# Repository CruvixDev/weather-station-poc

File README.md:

# Weather station POC (Proof Of Concept)

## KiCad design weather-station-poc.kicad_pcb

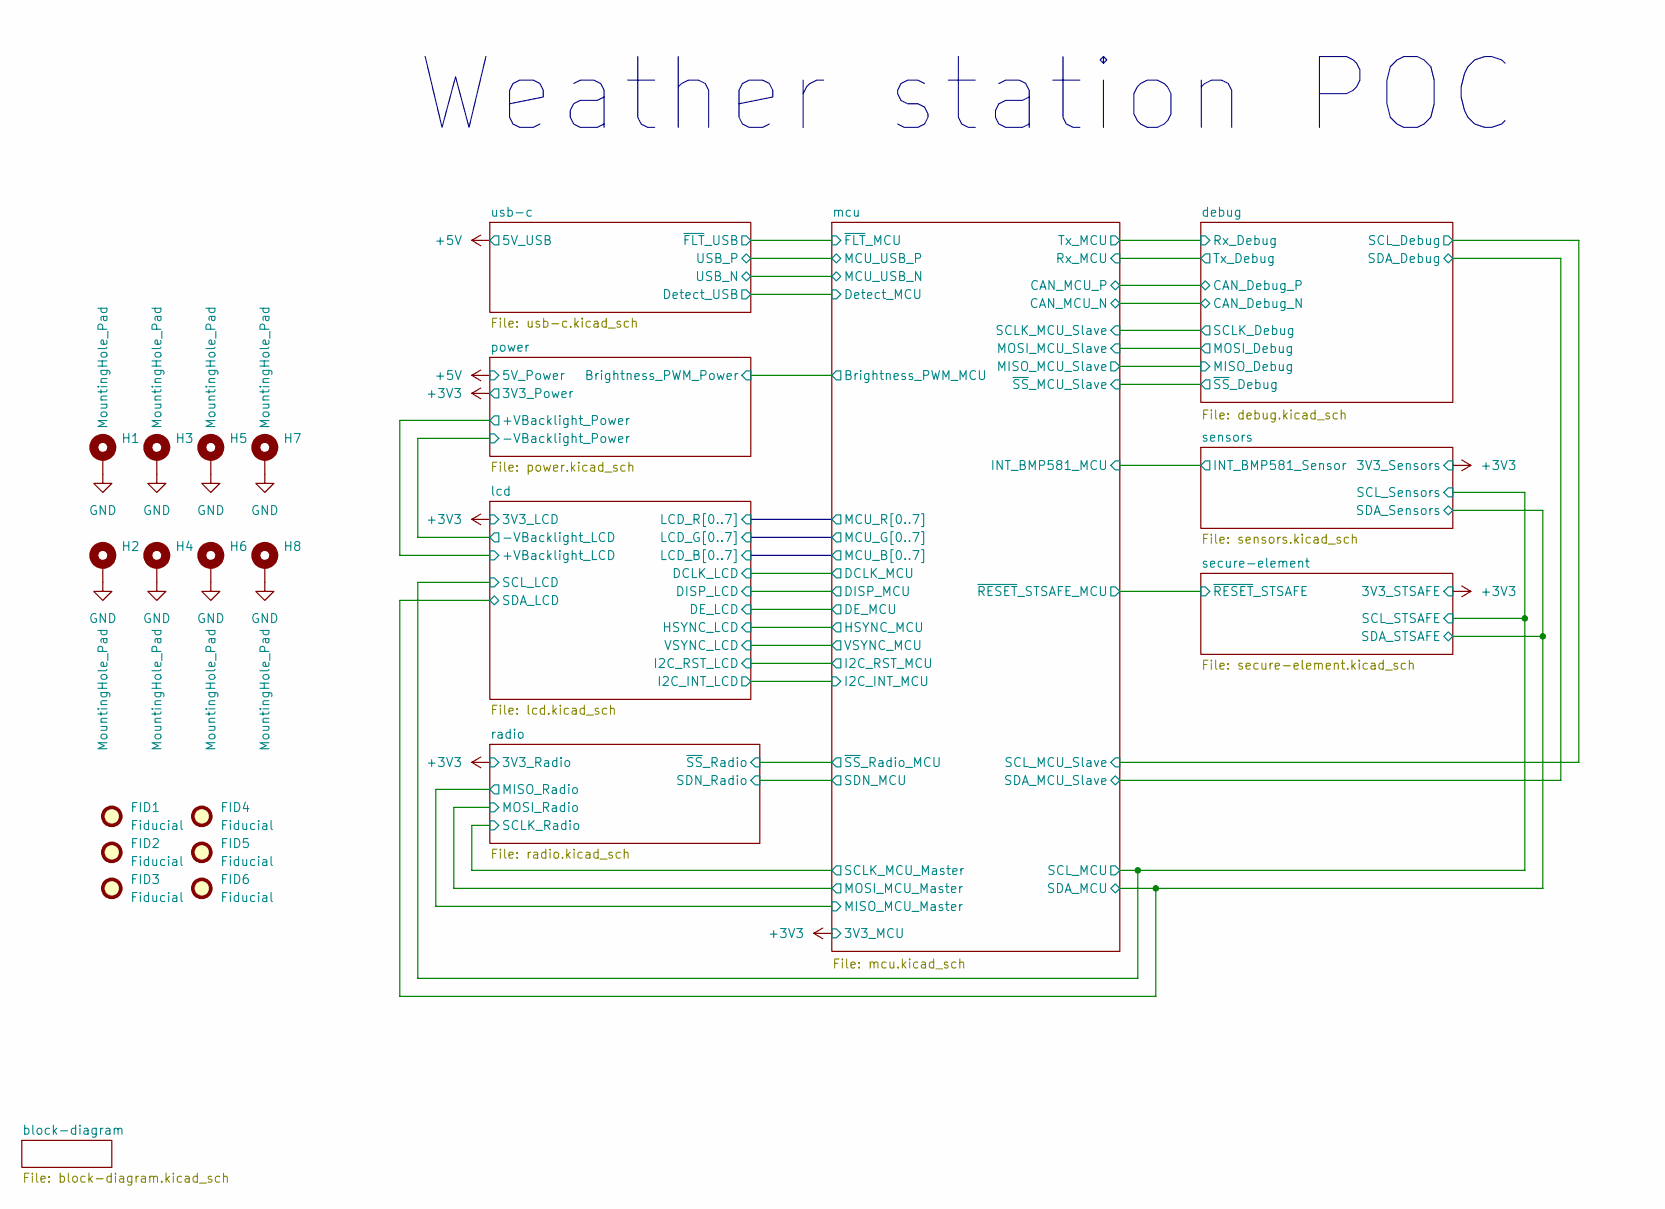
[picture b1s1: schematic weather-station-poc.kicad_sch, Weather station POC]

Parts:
FID1, FID2, FID3, FID4, FID5, FID6: Fiducial; Fiducial_1mm_Mask2mm; Manufacturer_Part_Number N/A
H1, H2, H3, H4, H5, H6, H7, H8: MountingHole_Pad; MountingHole_3.5mm_Pad_Via; Manufacturer_Part_Number N/A

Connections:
GND: H1.1 (1_1), H2.1 (1_1), H3.1 (1_1), H4.1 (1_1), H5.1 (1_1), H6.1 (1_1), H7.1 (1_1), H8.1 (1_1); also elsewhere on the board

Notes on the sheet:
Weather station POC

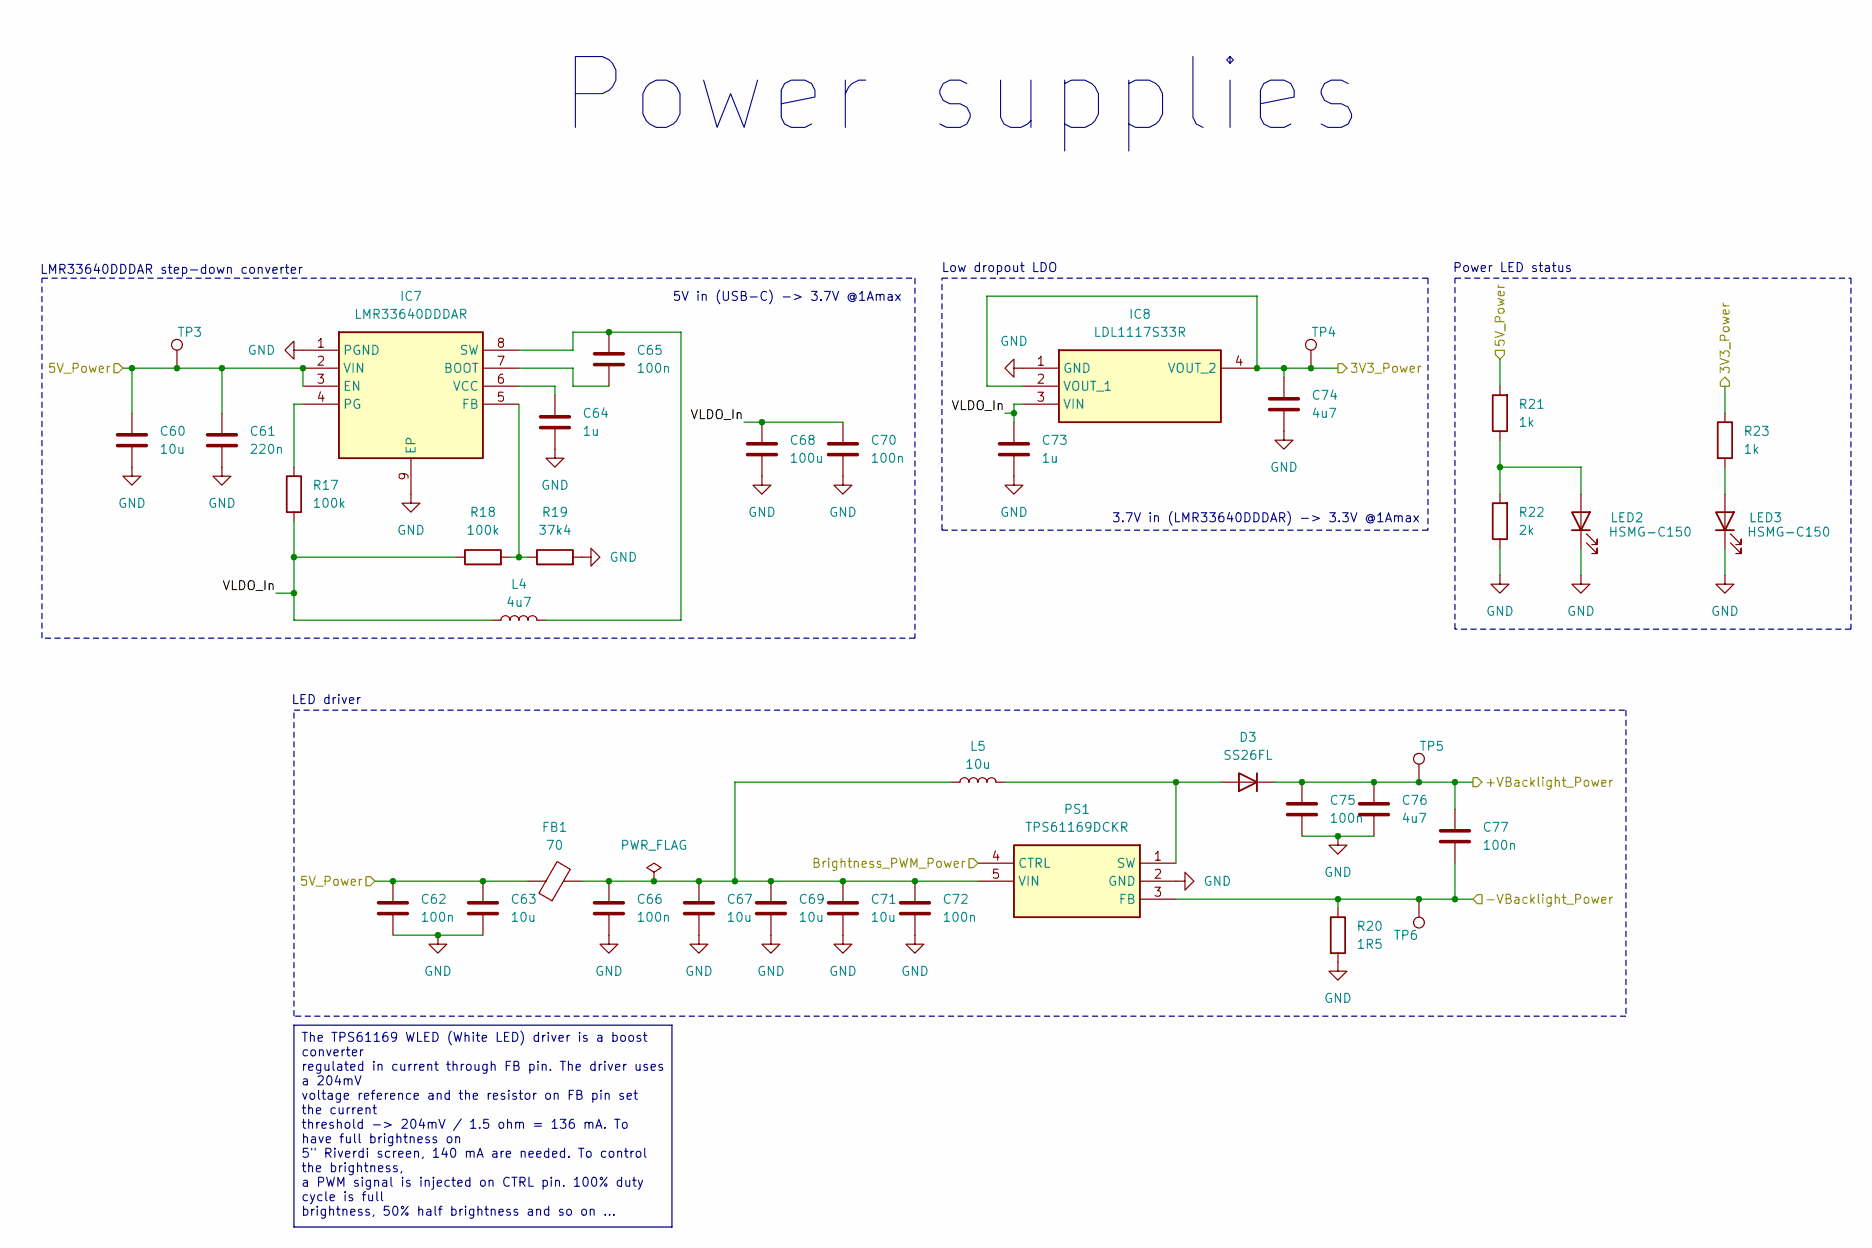
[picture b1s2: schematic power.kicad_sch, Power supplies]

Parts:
C60: 10u; C_0805_2012Metric_Pad1.18x1.45mm_HandSolder; Manufacturer_Part_Number C0805C106K8PACTU
C61: 220n; C_0402_1005Metric_Pad0.74x0.62mm_HandSolder; Manufacturer_Part_Number GRM155R61A224KE19D
C62, C66, C72, C75, C77: 100n; C_0603_1608Metric_Pad1.08x0.95mm_HandSolder; Manufacturer_Part_Number 885012206020
C63, C67, C69, C71: 10u; C_0603_1608Metric_Pad1.08x0.95mm_HandSolder; Manufacturer_Part_Number GRM188Z71A106KA73D
C64: 1u; C_0603_1608Metric_Pad1.08x0.95mm_HandSolder; Manufacturer_Part_Number GRM188R60J105KA01D
C65: 100n; C_0402_1005Metric_Pad0.74x0.62mm_HandSolder; Manufacturer_Part_Number GRM155R71A104KA01D
C68: 100u; C_1210_3225Metric_Pad1.33x2.70mm_HandSolder; Manufacturer_Part_Number GRM32EC80J107ME20L
C70: 100n; C_0603_1608Metric_Pad1.08x0.95mm_HandSolder; Manufacturer_Part_Number CGA3E2X7R1H104K080AA
C73: 1u; C_0603_1608Metric_Pad1.08x0.95mm_HandSolder; Manufacturer_Part_Number 885012206026
C74, C76: 4u7; C_0603_1608Metric_Pad1.08x0.95mm_HandSolder; Manufacturer_Part_Number GRM188Z71A475KE15J
D3: SS26FL; SODFL3617X108N; Mouser Part Number 512-SS26FL
FB1: 70; L_0603_1608Metric_Pad1.05x0.95mm_HandSolder; Part number BLM18SG700TN1D
IC7: LMR33640DDDAR; SOIC127P600X170-9N; Mouser Part Number 595-LMR33640DDDAR
IC8: LDL1117S33R; SOT230P700X180-4N; Mouser Part Number 511-LDL1117S33R
L4: 4u7; EXL1V06064R7R; Manufacturer_Part_Number EXL1V0606-4R7-R
L5: 10u; INDPM4040X180N; Manufacturer_Part_Number 74404042100
LED2, LED3: HSMG-C150; LEDC3216X120N; Mouser Part Number 630-HSMG-C150
PS1: TPS61169DCKR; SOT65P210X110-5N; Mouser Part Number 595-TPS61169DCKR
R17: 100k; R_0603_1608Metric_Pad0.98x0.95mm_HandSolder; Manufacturer_Part_Number CRCW0603100KFKEA
R18: 100k; R_0402_1005Metric_Pad0.72x0.64mm_HandSolder; Manufacturer_Part_Number CRCW0402100KFKED
R19: 37k4; R_0402_1005Metric_Pad0.72x0.64mm_HandSolder; Manufacturer_Part_Number CRCW040237K4FKED
R20: 1R5; R_0603_1608Metric_Pad0.98x0.95mm_HandSolder; Manufacturer_Part_Number ERJ-H3QD1R50V
R21, R23: 1k; R_0603_1608Metric_Pad0.98x0.95mm_HandSolder; Manufacturer_Part_Number 560112116014
R22: 2k; R_0603_1608Metric_Pad0.98x0.95mm_HandSolder; Manufacturer_Part_Number 560112116058
TP3, TP4, TP5, TP6: TestPoint; 5015; Manufacturer_Part_Number N/A

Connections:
+3V3: C74.1, IC8.2 (VOUT_1), IC8.4 (VOUT_2), R23.1, TP4.1 (1_1); also elsewhere on the board
+5V: C60.1, C61.1, C62.1, C63.1, FB1.1, IC7.2 (VIN), IC7.3 (EN), R21.2, TP3.1 (1_1); also elsewhere on the board
/lcd/+VBacklight_LCD: C75.1, C76.1, C77.1, D3.1 (K), TP5.1 (1_1); also elsewhere on the board
/lcd/-VBacklight_LCD: C77.2, PS1.3 (FB), R20.1, TP6.1 (1_1); also elsewhere on the board
/mcu/Brightness_PWM_MCU: PS1.4 (CTRL); also elsewhere on the board
/power/VLDO_In: C68.1, C70.1, C73.1, IC8.3 (VIN), L4.1, R17.2, R18.1
GND: C60.2, C61.2, C62.2, C63.2, C64.2, C66.2, C67.2, C68.2, C69.2, C70.2, C71.2, C72.2, C73.2, C74.2, C75.2, C76.2, IC7.1 (PGND), IC7.9 (EP), IC8.1 (GND), LED2.1 (K), LED3.1 (K), PS1.2 (GND), R19.2, R20.2, R22.1; also elsewhere on the board
unnamed: D3.2 (A), L5.2, PS1.1 (SW)
unnamed: C65.2, IC7.7 (BOOT)
unnamed: IC7.5 (FB), R18.2, R19.1
unnamed: IC7.4 (PG), R17.1
unnamed: C65.1, IC7.8 (SW), L4.2
unnamed: C64.1, IC7.6 (VCC)
unnamed: LED2.2 (A), R21.1, R22.2
unnamed: LED3.2 (A), R23.2
unnamed: C66.1, C67.1, C69.1, C71.1, C72.1, FB1.2, L5.1, PS1.5 (VIN)

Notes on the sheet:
Power supplies
3.7V in (LMR33640DDDAR) -> 3.3V @1Amax
LED driver
Low dropout LDO
LMR33640DDDAR step-down converter
5V in (USB-C) -> 3.7V @1Amax
Power LED status
The TPS61169 WLED (White LED) driver is a boost converter regulated in current through FB pin. The driver uses a 204mV voltage reference and the resistor on FB pin set the current threshold -> 204mV / 1.5 ohm = 136 mA. To have full brightness on 5" Riverdi screen, 140 mA are needed. To control the 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

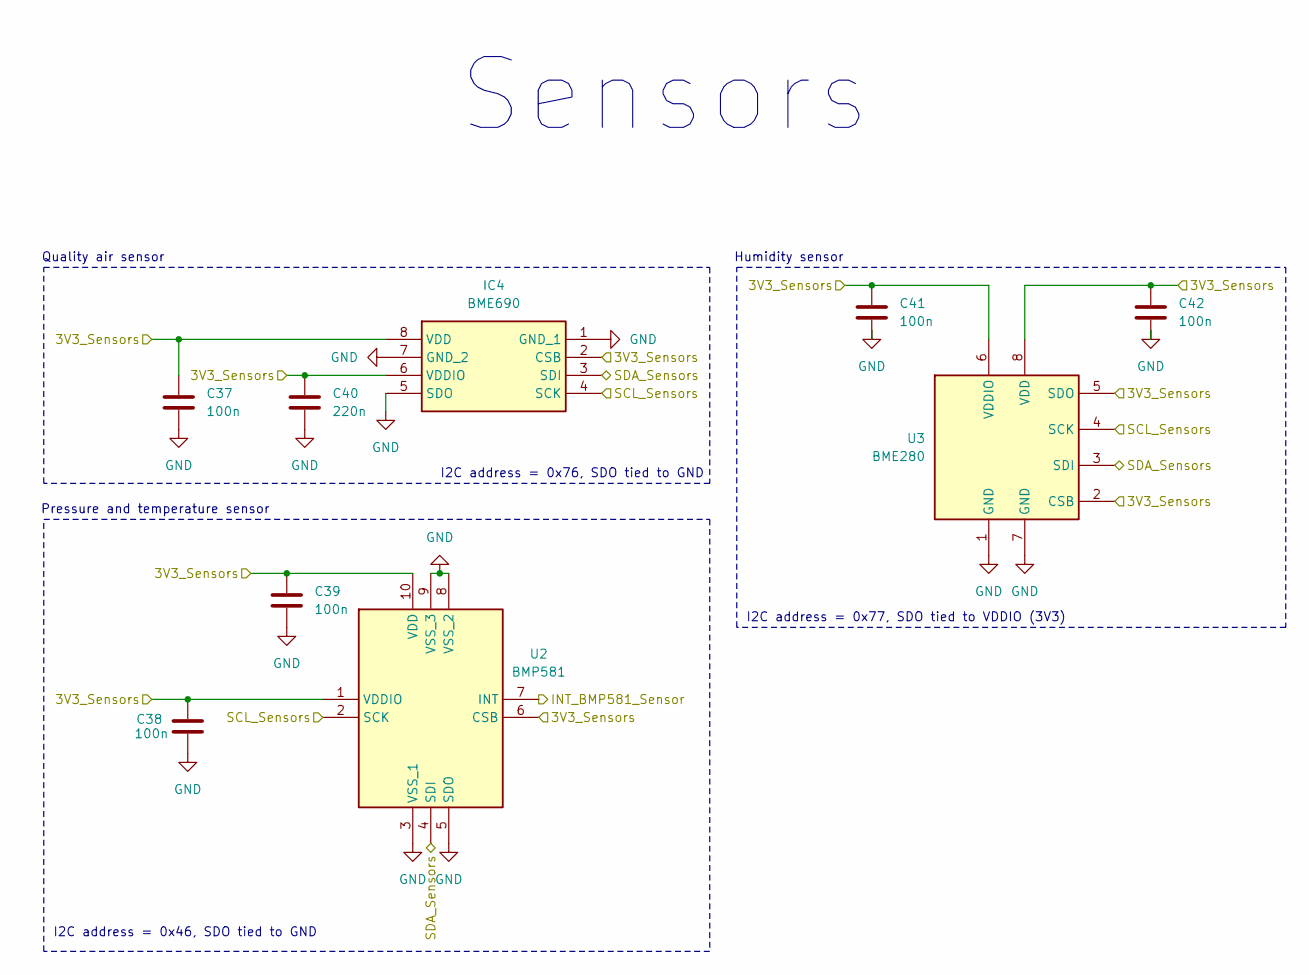
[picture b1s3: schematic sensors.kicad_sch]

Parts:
C37, C38, C39, C41, C42: 100n; C_0603_1608Metric_Pad1.08x0.95mm_HandSolder; Manufacturer_Part_Number 885012206020
C40: 220n; C_0603_1608Metric_Pad1.08x0.95mm_HandSolder; Manufacturer_Part_Number 885012206022
IC4: BME690; Mouser Part Number 262-BME690
U2: BMP581; Mouser Part Number 262-BMP581
U3: BME280; Bosch_LGA-8_2.5x2.5mm_P0.65mm_ClockwisePinNumbering; Manufacturer_Part_Number BME280

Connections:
+3V3: C37.1, C38.1, C39.1, C40.1, C41.1, C42.1, IC4.2 (CSB), IC4.6 (VDDIO), IC4.8 (VDD), U2.1 (VDDIO), U2.6 (CSB), U2.10 (VDD), U3.2 (CSB), U3.5 (SDO), U3.6 (VDDIO), U3.8 (VDD); also elsewhere on the board
/lcd/SCL_LCD: IC4.4 (SCK), U2.2 (SCK), U3.4 (SCK); also elsewhere on the board
/lcd/SDA_LCD: IC4.3 (SDI), U2.4 (SDI), U3.3 (SDI); also elsewhere on the board
/mcu/INT_BMP581_MCU: U2.7 (INT); also elsewhere on the board
GND: C37.2, C38.2, C39.2, C40.2, C41.2, C42.2, IC4.1 (GND_1), IC4.5 (SDO), IC4.7 (GND_2), U2.3 (VSS_1), U2.5 (SDO), U2.8 (VSS_2), U2.9 (VSS_3), U3.1 (GND), U3.7 (GND); also elsewhere on the board

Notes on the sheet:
I2C address = 0x77, SDO tied to VDDIO (3V3)
Humidity sensor
Pressure and temperature sensor
I2C address = 0x46, SDO tied to GND
Sensors
Quality air sensor
I2C address = 0x76, SDO tied to GND

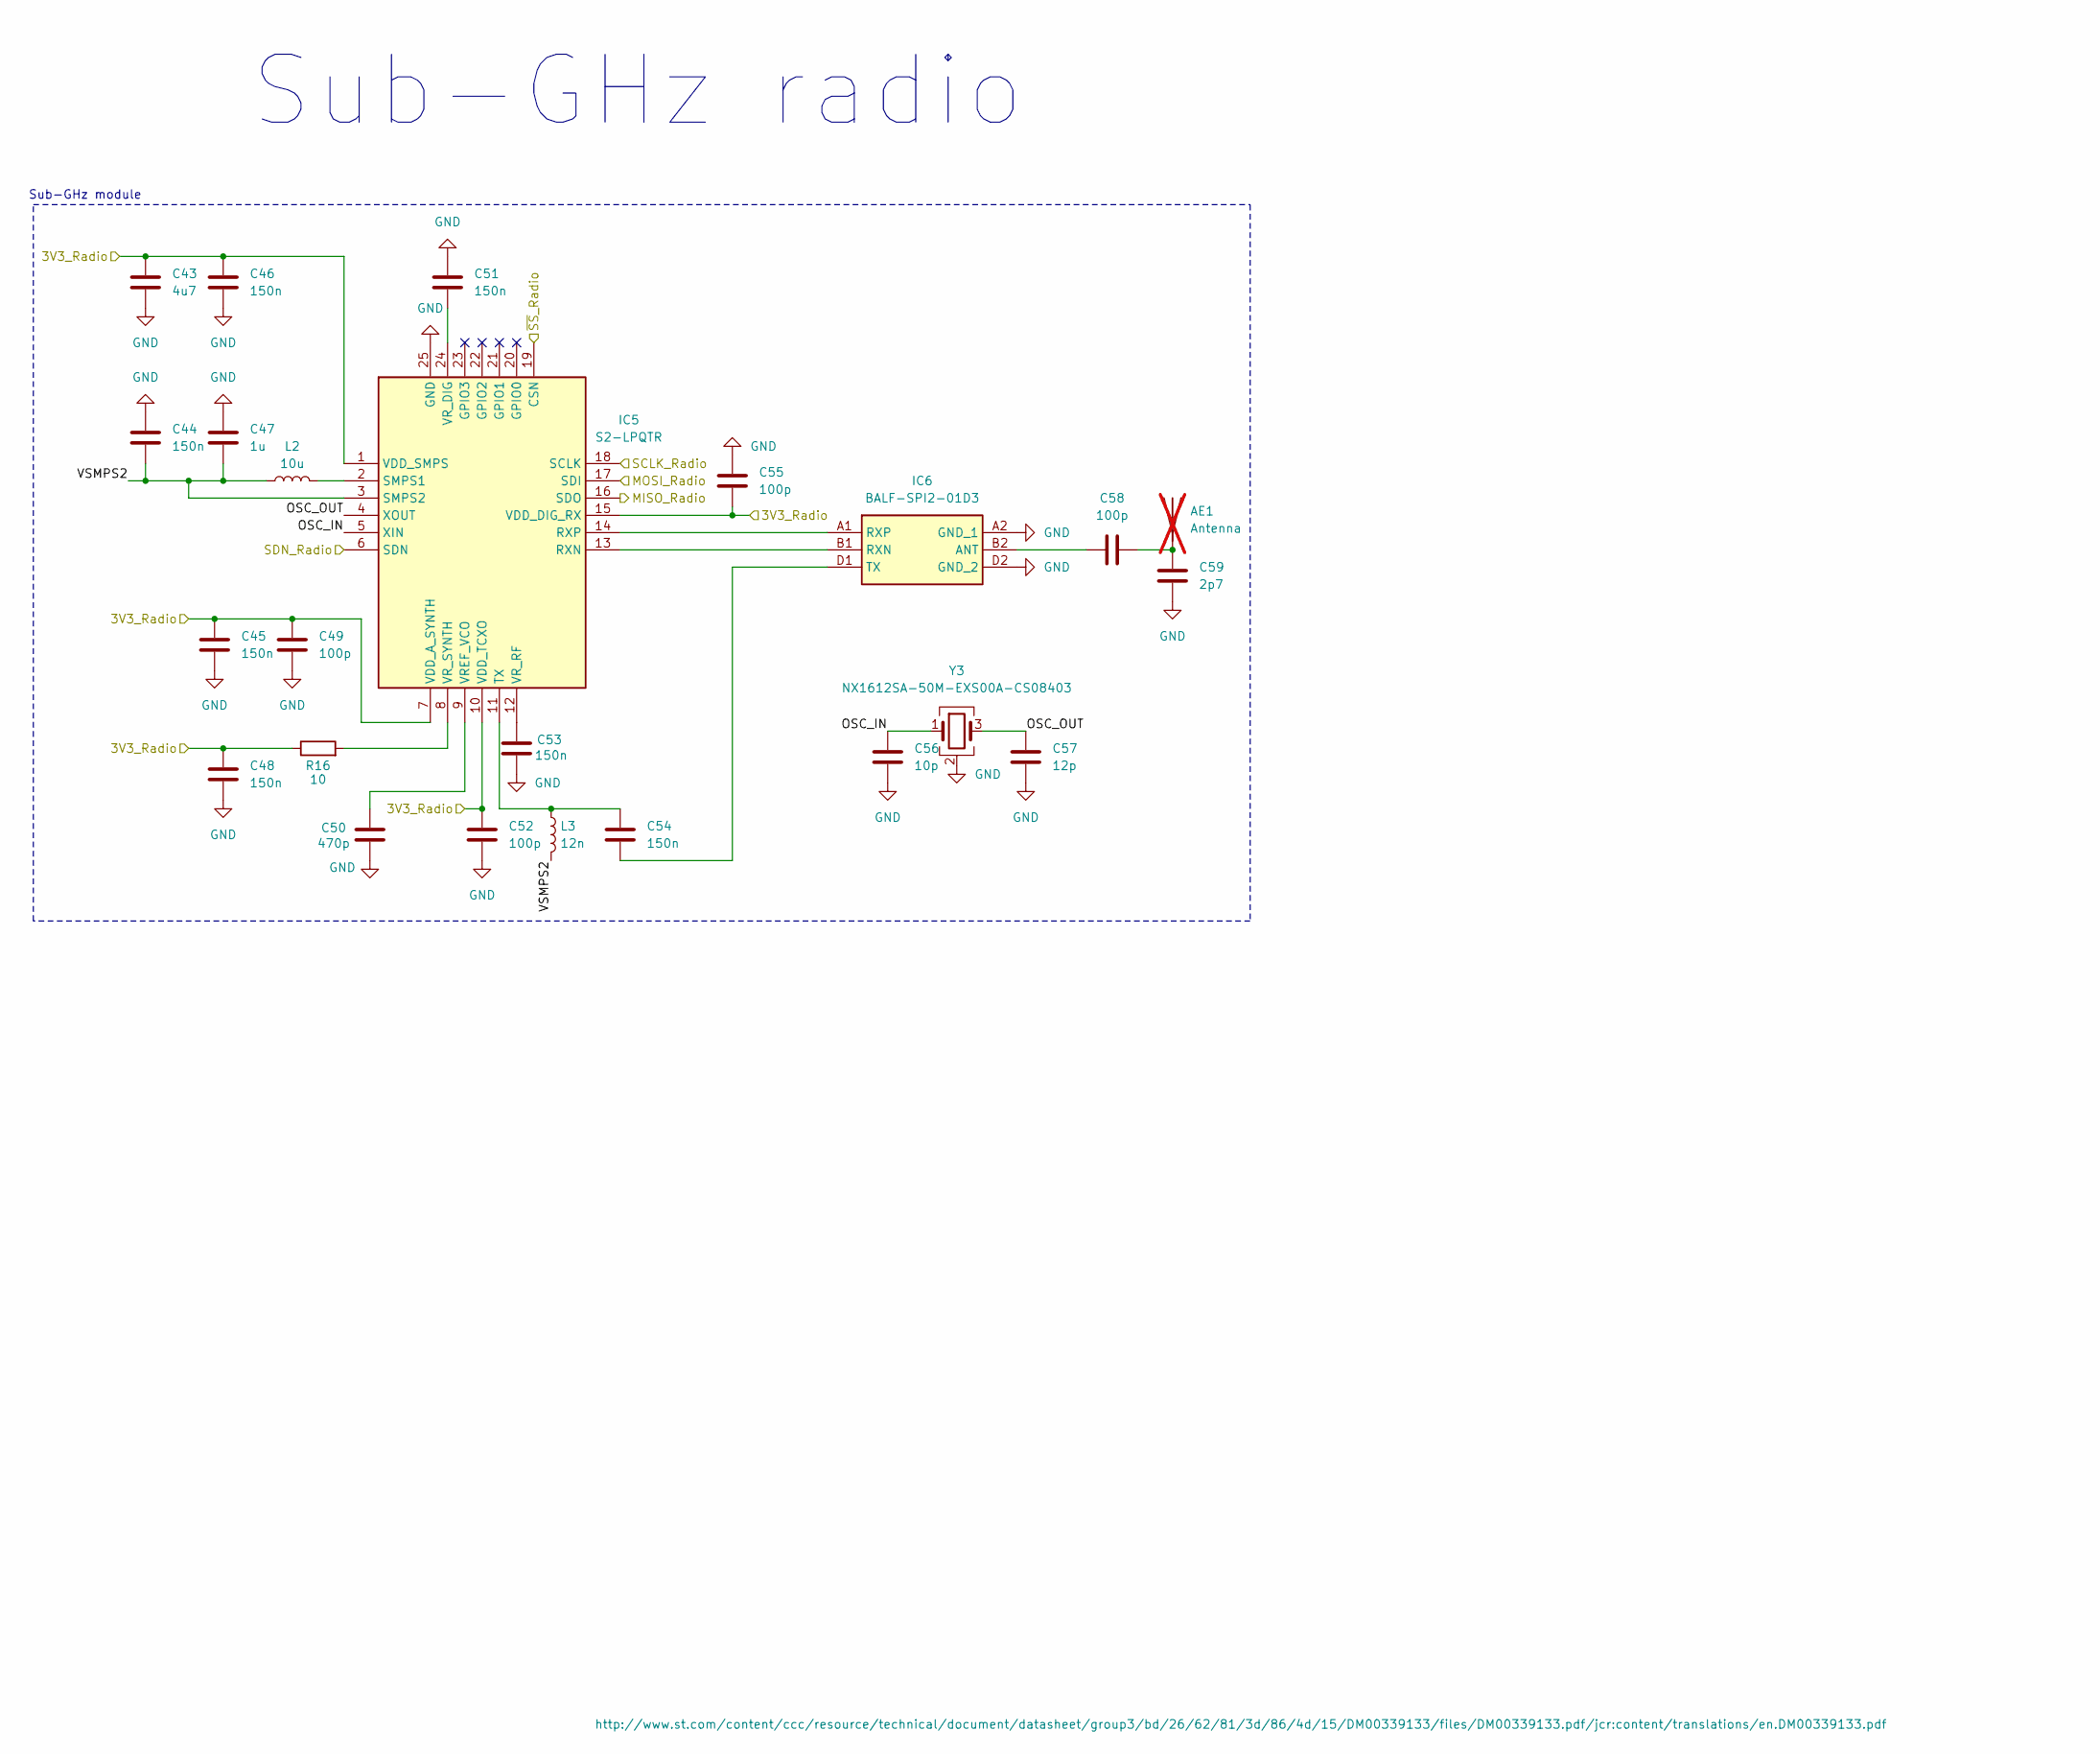
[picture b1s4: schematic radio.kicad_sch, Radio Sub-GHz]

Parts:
AE1: Antenna; SMA_Molex_73251-1153_EdgeMount_Horizontal; Manufacturer_Part_Number 73251-1153; not fitted
C43: 4u7; C_0603_1608Metric_Pad1.08x0.95mm_HandSolder; Manufacturer_Part_Number GRM188Z71A475KE15J
C44, C45, C46, C48, C51, C53, C54: 150n; C_0603_1608Metric_Pad1.08x0.95mm_HandSolder; Manufacturer_Part_Number 885012206021
C47: 1u; C_0603_1608Metric_Pad1.08x0.95mm_HandSolder; Manufacturer_Part_Number 885012206026
C49, C52, C55, C58: 100p; C_0603_1608Metric_Pad1.08x0.95mm_HandSolder; Manufacturer_Part_Number 885012206003
C50: 470p; C_0603_1608Metric_Pad1.08x0.95mm_HandSolder; Manufacturer_Part_Number 885012206006
C56: 10p; C_0603_1608Metric_Pad1.08x0.95mm_HandSolder; Manufacturer_Part_Number 885012006002
C57: 12p; C_0603_1608Metric_Pad1.08x0.95mm_HandSolder; Manufacturer_Part_Number VJ0603A120FXQCW1BC
C59: 2p7; C_0603_1608Metric_Pad1.08x0.95mm_HandSolder; Manufacturer_Part_Number VJ0603A2R7BXQCW1BC
IC5: S2-LPQTR; QFN50P400X400X100-25N-D; Mouser Part Number 511-S2-LPQTR
IC6: BALF-SPI2-01D3; BALFSPI201D3; Mouser Part Number 511-BALF-SPI2-01D3
L2: 10u; L_0805_2012Metric_Pad1.05x1.20mm_HandSolder; Manufacturer_Part_Number LQM21FN100M80L
L3: 12n; L_0603_1608Metric_Pad1.05x0.95mm_HandSolder; Manufacturer_Part_Number LQW18AN12NG00D
R16: 10; R_0603_1608Metric_Pad0.98x0.95mm_HandSolder; Manufacturer_Part_Number 560050316012
Y3: NX1612SA-50M-EXS00A-CS08403; NX1612SA50MEXS00ACS08403; Mouser Part Number 344-NX1612SA50S08403

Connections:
+3V3: C43.1, C45.1, C46.1, C48.1, C49.1, C52.1, C55.2, IC5.1 (VDD_SMPS), IC5.7 (VDD_A_SYNTH), IC5.10 (VDD_TCXO), IC5.15 (VDD_DIG_RX), R16.1; also elsewhere on the board
/mcu/MISO_MCU_Master: IC5.16 (SDO); also elsewhere on the board
/mcu/MOSI_MCU_Master: IC5.17 (SDI); also elsewhere on the board
/mcu/SCLK_MCU_Master: IC5.18 (SCLK); also elsewhere on the board
/mcu/SDN_MCU: IC5.6 (SDN); also elsewhere on the board
/mcu/~SS_Radio_MCU: IC5.19 (CSN); also elsewhere on the board
/radio/OSC_IN: C56.1, IC5.5 (XIN), Y3.1
/radio/OSC_OUT: C57.2, IC5.4 (XOUT), Y3.3
/radio/VSMPS2: C44.1, C47.1, IC5.3 (SMPS2), L2.1, L3.2
GND: C43.2, C44.2, C45.2, C46.2, C47.2, C48.2, C49.2, C50.1, C51.2, C52.2, C53.1, C55.1, C56.2, C57.1, C59.1, IC5.25 (GND), IC6.A2 (GND_1), IC6.D2 (GND_2), Y3.2 (G), Y3.4 (G); also elsewhere on the board
unnamed: AE1.1 (A_1), C58.1, C59.2
unnamed: IC5.13 (RXN), IC6.B1 (RXN)
unnamed: IC5.14 (RXP), IC6.A1 (RXP)
unnamed: IC5.2 (SMPS1), L2.2
unnamed: C54.2, IC5.11 (TX), L3.1
unnamed: C50.2, IC5.9 (VREF_VCO)
unnamed: C51.1, IC5.24 (VR_DIG)
unnamed: C53.2, IC5.12 (VR_RF)
unnamed: IC5.8 (VR_SYNTH), R16.2
unnamed: C58.2, IC6.B2 (ANT)
unnamed: C54.1, IC6.D1 (TX)

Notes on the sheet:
Sub-GHz radio
Sub-GHz module

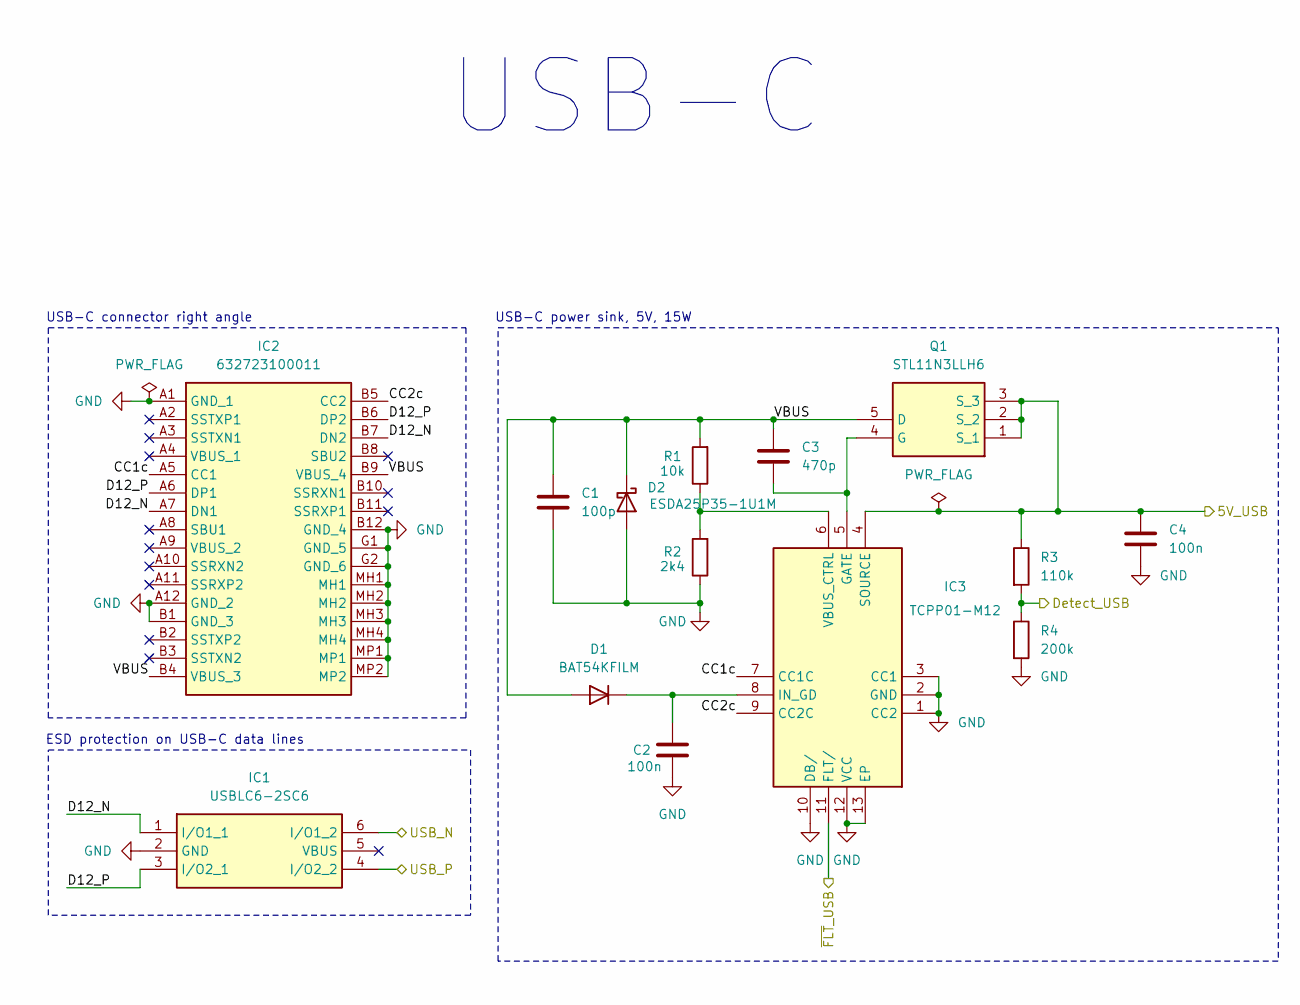
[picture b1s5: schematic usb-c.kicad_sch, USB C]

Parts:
C1: 100p; C_0603_1608Metric_Pad1.08x0.95mm_HandSolder; Manufacturer_Part_Number 885012206003
C2, C4: 100n; C_0603_1608Metric_Pad1.08x0.95mm_HandSolder; Manufacturer_Part_Number 885012206020
C3: 470p; C_0603_1608Metric_Pad1.08x0.95mm_HandSolder; Manufacturer_Part_Number 885012206006
D1: BAT54KFILM; SODFL1608X70N; Mouser Part Number 511-BAT54KFILM
D2: ESDA25P35-1U1M; ESDA25P351U1M; Mouser Part Number 511-ESDA25P35-1U1M
IC1: USBLC6-2SC6; SOT95P280X145-6N; Manufacturer_Part_Number USBLC6-2SC6; Mouser Part Number 511-USBLC6-2SC6
IC2: 632723100011; Mouser Part Number 710-632723100011
IC3: TCPP01-M12; QFN50P300X300X100-13N-D; Manufacturer_Part_Number TCPP01-M12; Mouser Part Number 511-TCPP01-M12
Q1: STL11N3LLH6; STL20N6F7; Manufacturer_Part_Number STL11N3LLH6; Mouser Part Number 511-STL11N3LLH6
R1: 10k; R_0603_1608Metric_Pad0.98x0.95mm_HandSolder; Manufacturer_Part_Number 560112116005
R2: 2k4; R_0603_1608Metric_Pad0.98x0.95mm_HandSolder; Manufacturer_Part_Number 560112116061
R3: 110k; R_0603_1608Metric_Pad0.98x0.95mm_HandSolder; Manufacturer_Part_Number 560112116148
R4: 200k; R_0603_1608Metric_Pad0.98x0.95mm_HandSolder; Manufacturer_Part_Number 560112116060

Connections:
+5V: C4.1, IC3.4 (SOURCE), Q1.1 (S_1), Q1.2 (S_2), Q1.3 (S_3), R3.1; also elsewhere on the board
/mcu/Detect_MCU: R3.2, R4.1; also elsewhere on the board
/mcu/MCU_USB_N: IC1.6 (I/O1_2); also elsewhere on the board
/mcu/MCU_USB_P: IC1.4 (I/O2_2); also elsewhere on the board
/mcu/~FLT_MCU: IC3.11 (FLT/); also elsewhere on the board
/usb-c/CC1c: IC2.A5 (CC1), IC3.7 (CC1C)
/usb-c/CC2c: IC2.B5 (CC2), IC3.9 (CC2C)
/usb-c/D12_N: IC1.1 (I/O1_1), IC2.A7 (DN1), IC2.B7 (DN2)
/usb-c/D12_P: IC1.3 (I/O2_1), IC2.A6 (DP1), IC2.B6 (DP2)
/usb-c/VBUS: C1.1, C3.1, D1.2 (A), D2.1 (K), IC2.B4 (VBUS_3), IC2.B9 (VBUS_4), Q1.5 (D), R1.2
GND: C1.2, C2.2, C4.2, D2.2 (A), IC1.2 (GND), IC2.A1 (GND_1), IC2.A12 (GND_2), IC2.B1 (GND_3), IC2.B12 (GND_4), IC2.G1 (GND_5), IC2.G2 (GND_6), IC2.MH1, IC2.MH2, IC2.MH3, IC2.MH4, IC2.MP1, IC2.MP2, IC3.1 (CC2), IC3.2 (GND), IC3.3 (CC1), IC3.10 (DB/), IC3.12 (VCC), IC3.13 (EP), R2.1, R4.2; also elsewhere on the board
unnamed: C2.1, D1.1 (K), IC3.8 (IN_GD)
unnamed: C3.2, IC3.5 (GATE), Q1.4 (G)
unnamed: IC3.6 (VBUS_CTRL), R1.1, R2.2

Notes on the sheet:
USB-C connector right angle
USB-C
ESD protection on USB-C data lines
USB-C power sink, 5V, 15W
